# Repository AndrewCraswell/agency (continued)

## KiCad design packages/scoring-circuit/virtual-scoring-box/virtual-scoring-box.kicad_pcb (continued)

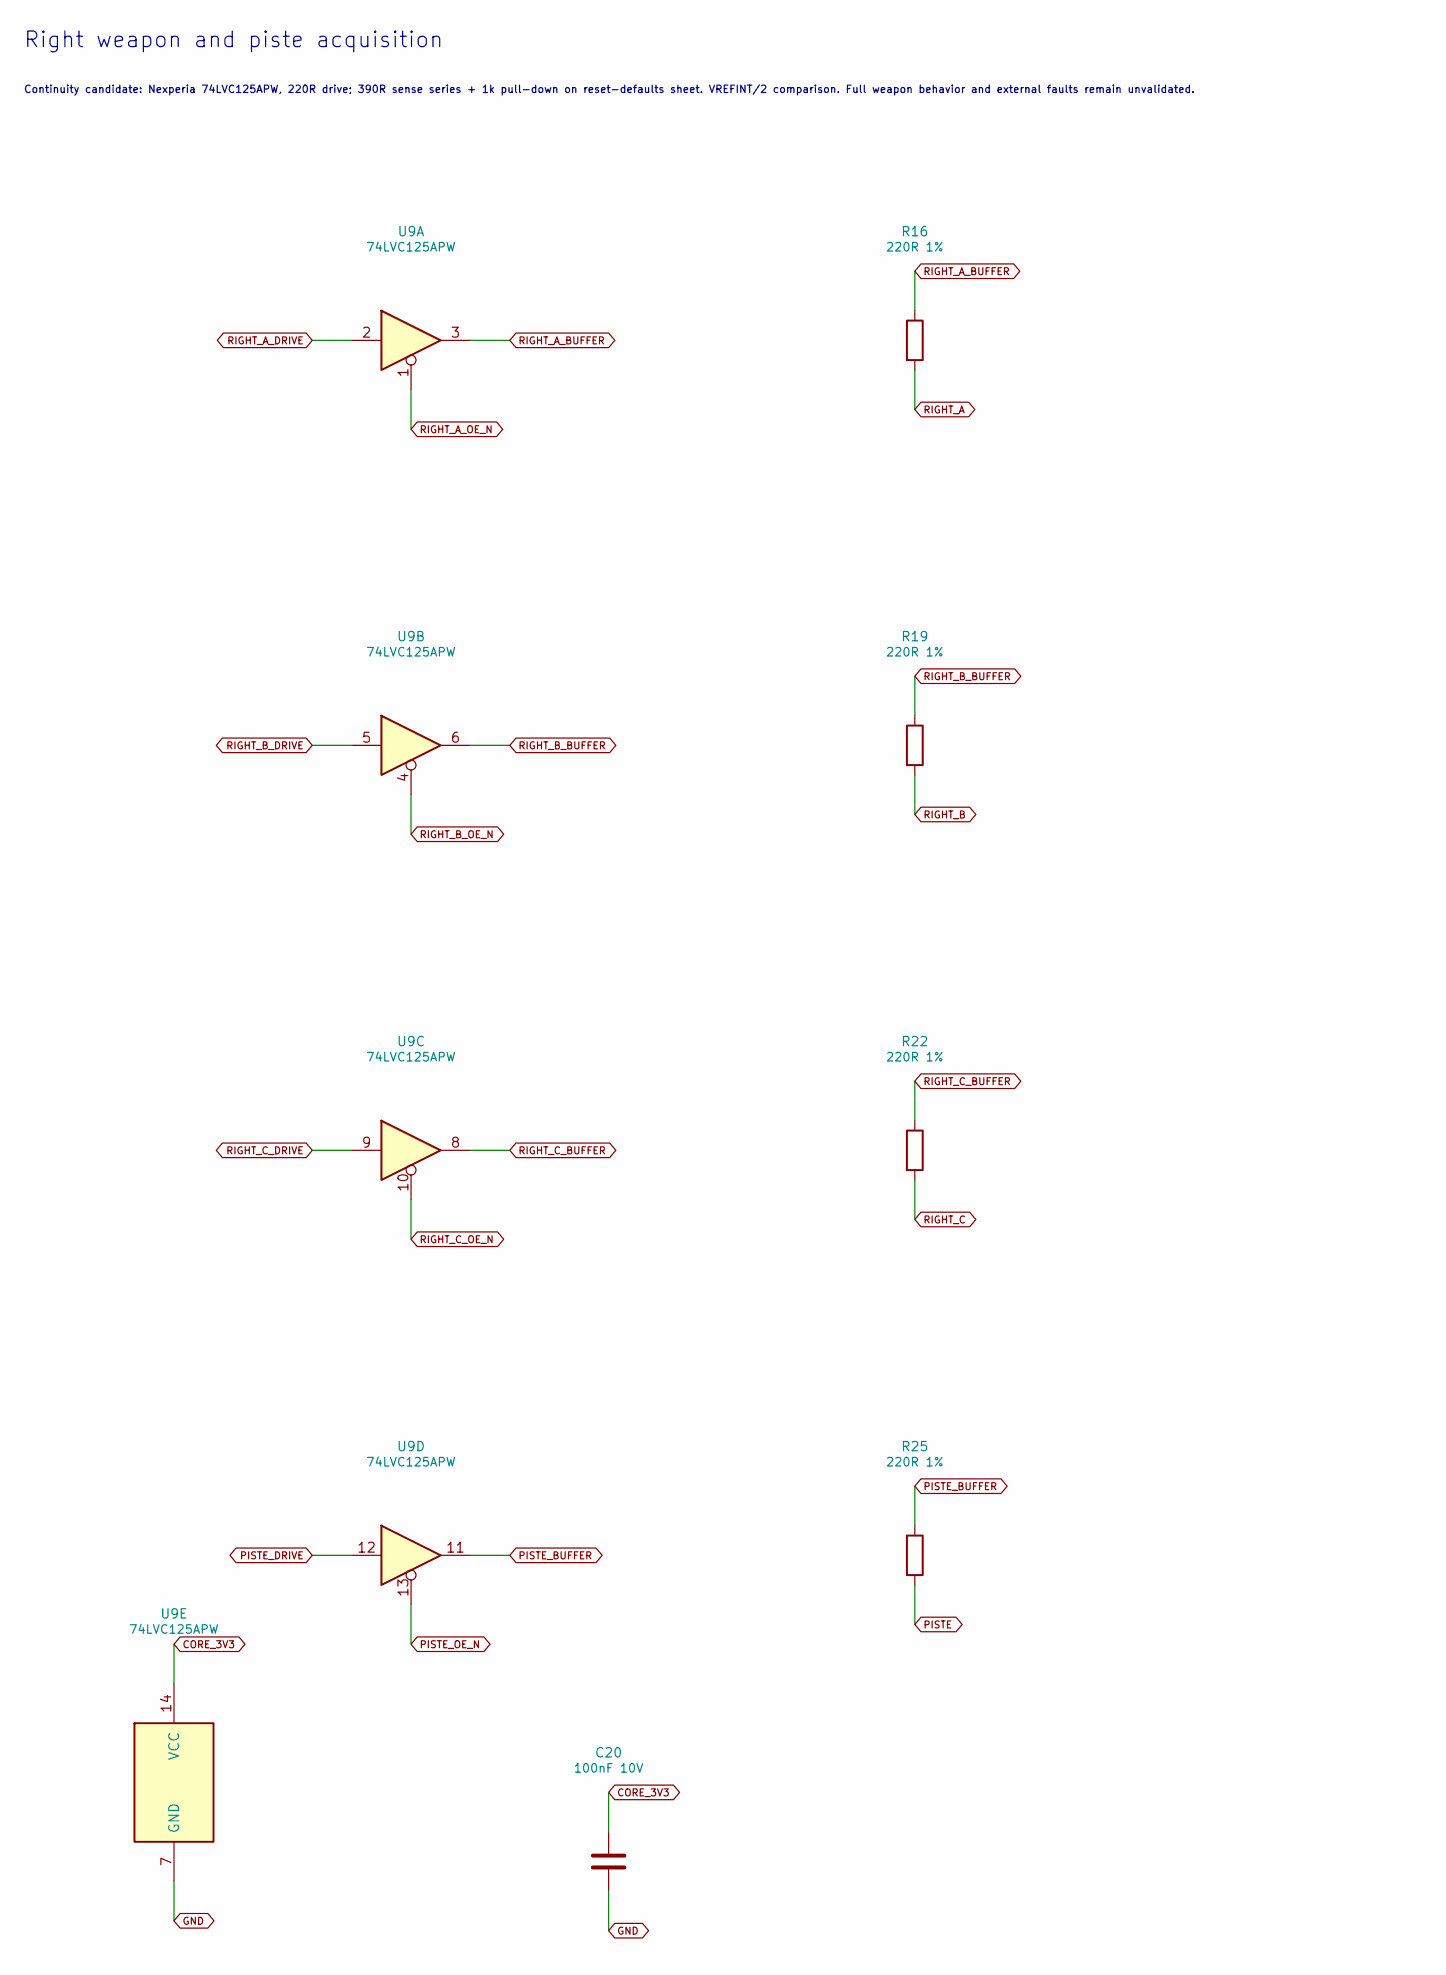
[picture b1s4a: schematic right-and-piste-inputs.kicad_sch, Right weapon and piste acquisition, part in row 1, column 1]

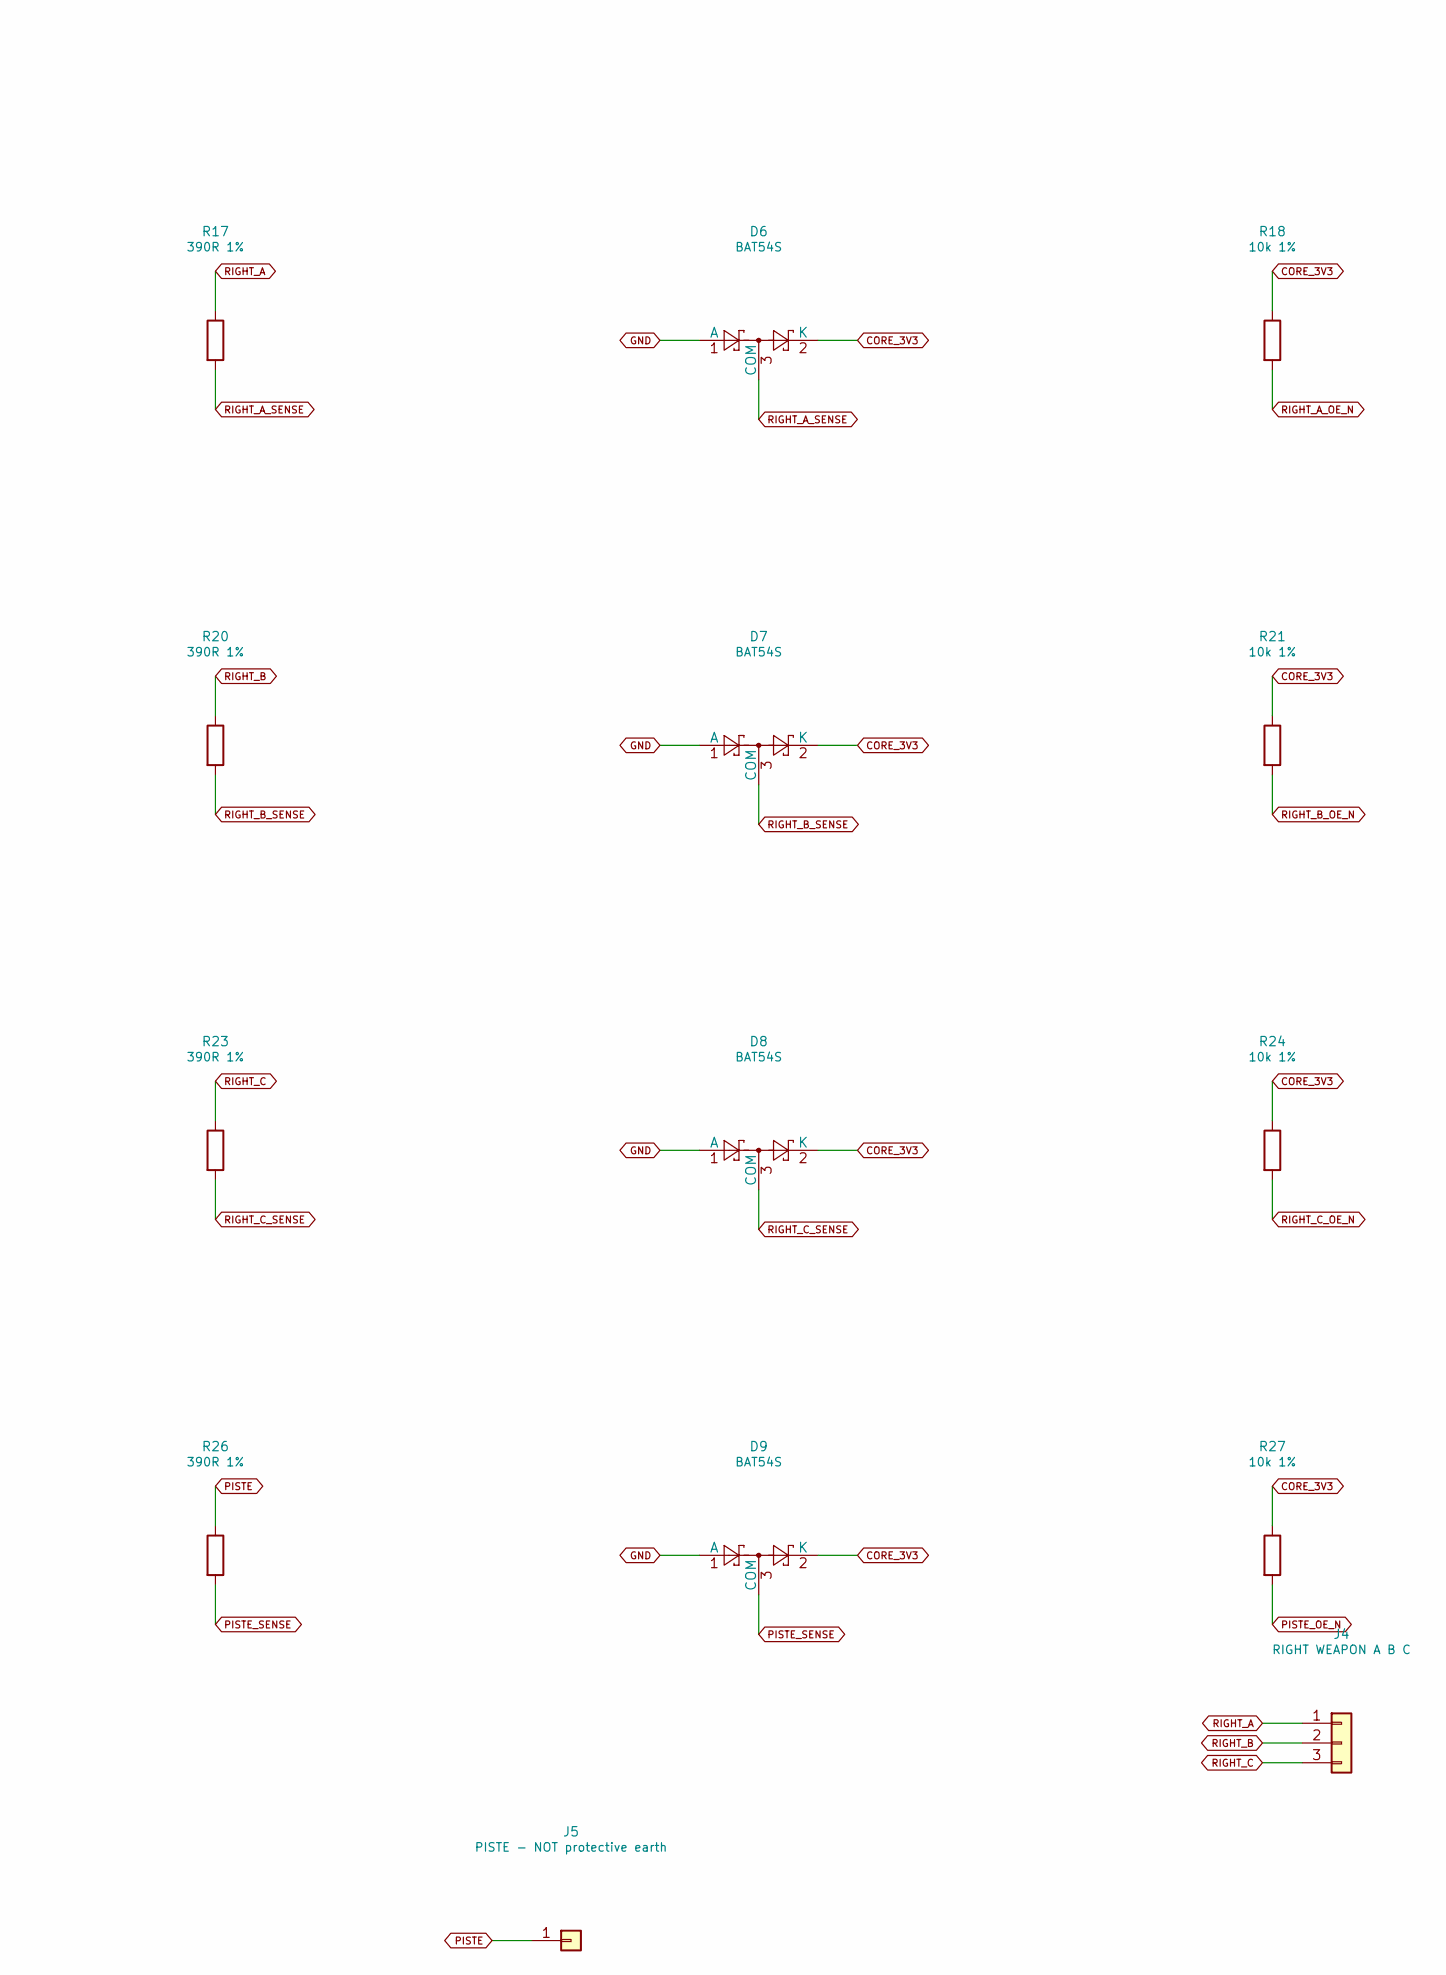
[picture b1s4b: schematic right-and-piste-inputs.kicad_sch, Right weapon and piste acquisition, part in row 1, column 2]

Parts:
C20: 100nF 10V; C_0603_1608Metric; MPN CC0603KRX7R9BB104
D6, D7, D8, D9: BAT54S; SOT-23; MPN BAT54S,215
J4: RIGHT WEAPON A B C; Wire_Solder_3; MPN PCB solder termination
J5: PISTE - NOT protective earth; Wire_Solder_1; MPN PCB solder termination
R16, R19, R22, R25: 220R 1%; R_0603_1608Metric; MPN ERJPA3F2200V
R17, R20, R23, R26: 390R 1%; R_0603_1608Metric; MPN RC0603FR-07390RL
R18, R21, R24, R27: 10k 1%; R_0603_1608Metric; MPN RC0603FR-0710KL
U9: 74LVC125APW; TSSOP-14_4.4x5mm_P0.65mm; MPN 74LVC125APW,118

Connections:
CORE_3V3: C20.1, D6.2 (K), D7.2 (K), D8.2 (K), D9.2 (K), R18.1, R21.1, R24.1, R27.1, U9.14 (VCC); also elsewhere on the board
GND: C20.2, D6.1 (A), D7.1 (A), D8.1 (A), D9.1 (A), U9.7 (GND); also elsewhere on the board
PISTE: J5.1 (Pin_1_1), R25.2, R26.1
PISTE_BUFFER: R25.1, U9.11
PISTE_DRIVE: U9.12; also elsewhere on the board
PISTE_OE_N: R27.2, U9.13; also elsewhere on the board
PISTE_SENSE: D9.3 (COM), R26.2; also elsewhere on the board
RIGHT_A: J4.1, R16.2, R17.1
RIGHT_A_BUFFER: R16.1, U9.3
RIGHT_A_DRIVE: U9.2; also elsewhere on the board
RIGHT_A_OE_N: R18.2, U9.1; also elsewhere on the board
RIGHT_A_SENSE: D6.3 (COM), R17.2; also elsewhere on the board
RIGHT_B: J4.2, R19.2, R20.1
RIGHT_B_BUFFER: R19.1, U9.6
RIGHT_B_DRIVE: U9.5; also elsewhere on the board
RIGHT_B_OE_N: R21.2, U9.4; also elsewhere on the board
RIGHT_B_SENSE: D7.3 (COM), R20.2; also elsewhere on the board
RIGHT_C: J4.3, R22.2, R23.1
RIGHT_C_BUFFER: R22.1, U9.8
RIGHT_C_DRIVE: U9.9; also elsewhere on the board
RIGHT_C_OE_N: R24.2, U9.10; also elsewhere on the board
RIGHT_C_SENSE: D8.3 (COM), R23.2; also elsewhere on the board

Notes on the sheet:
Right weapon and piste acquisition
Continuity candidate: Nexperia 74LVC125APW, 220R drive; 390R sense series + 1k pull-down on reset-defaults sheet. VREFINT/2 comparison. Full weapon behavior and external faults remain unvalidated.

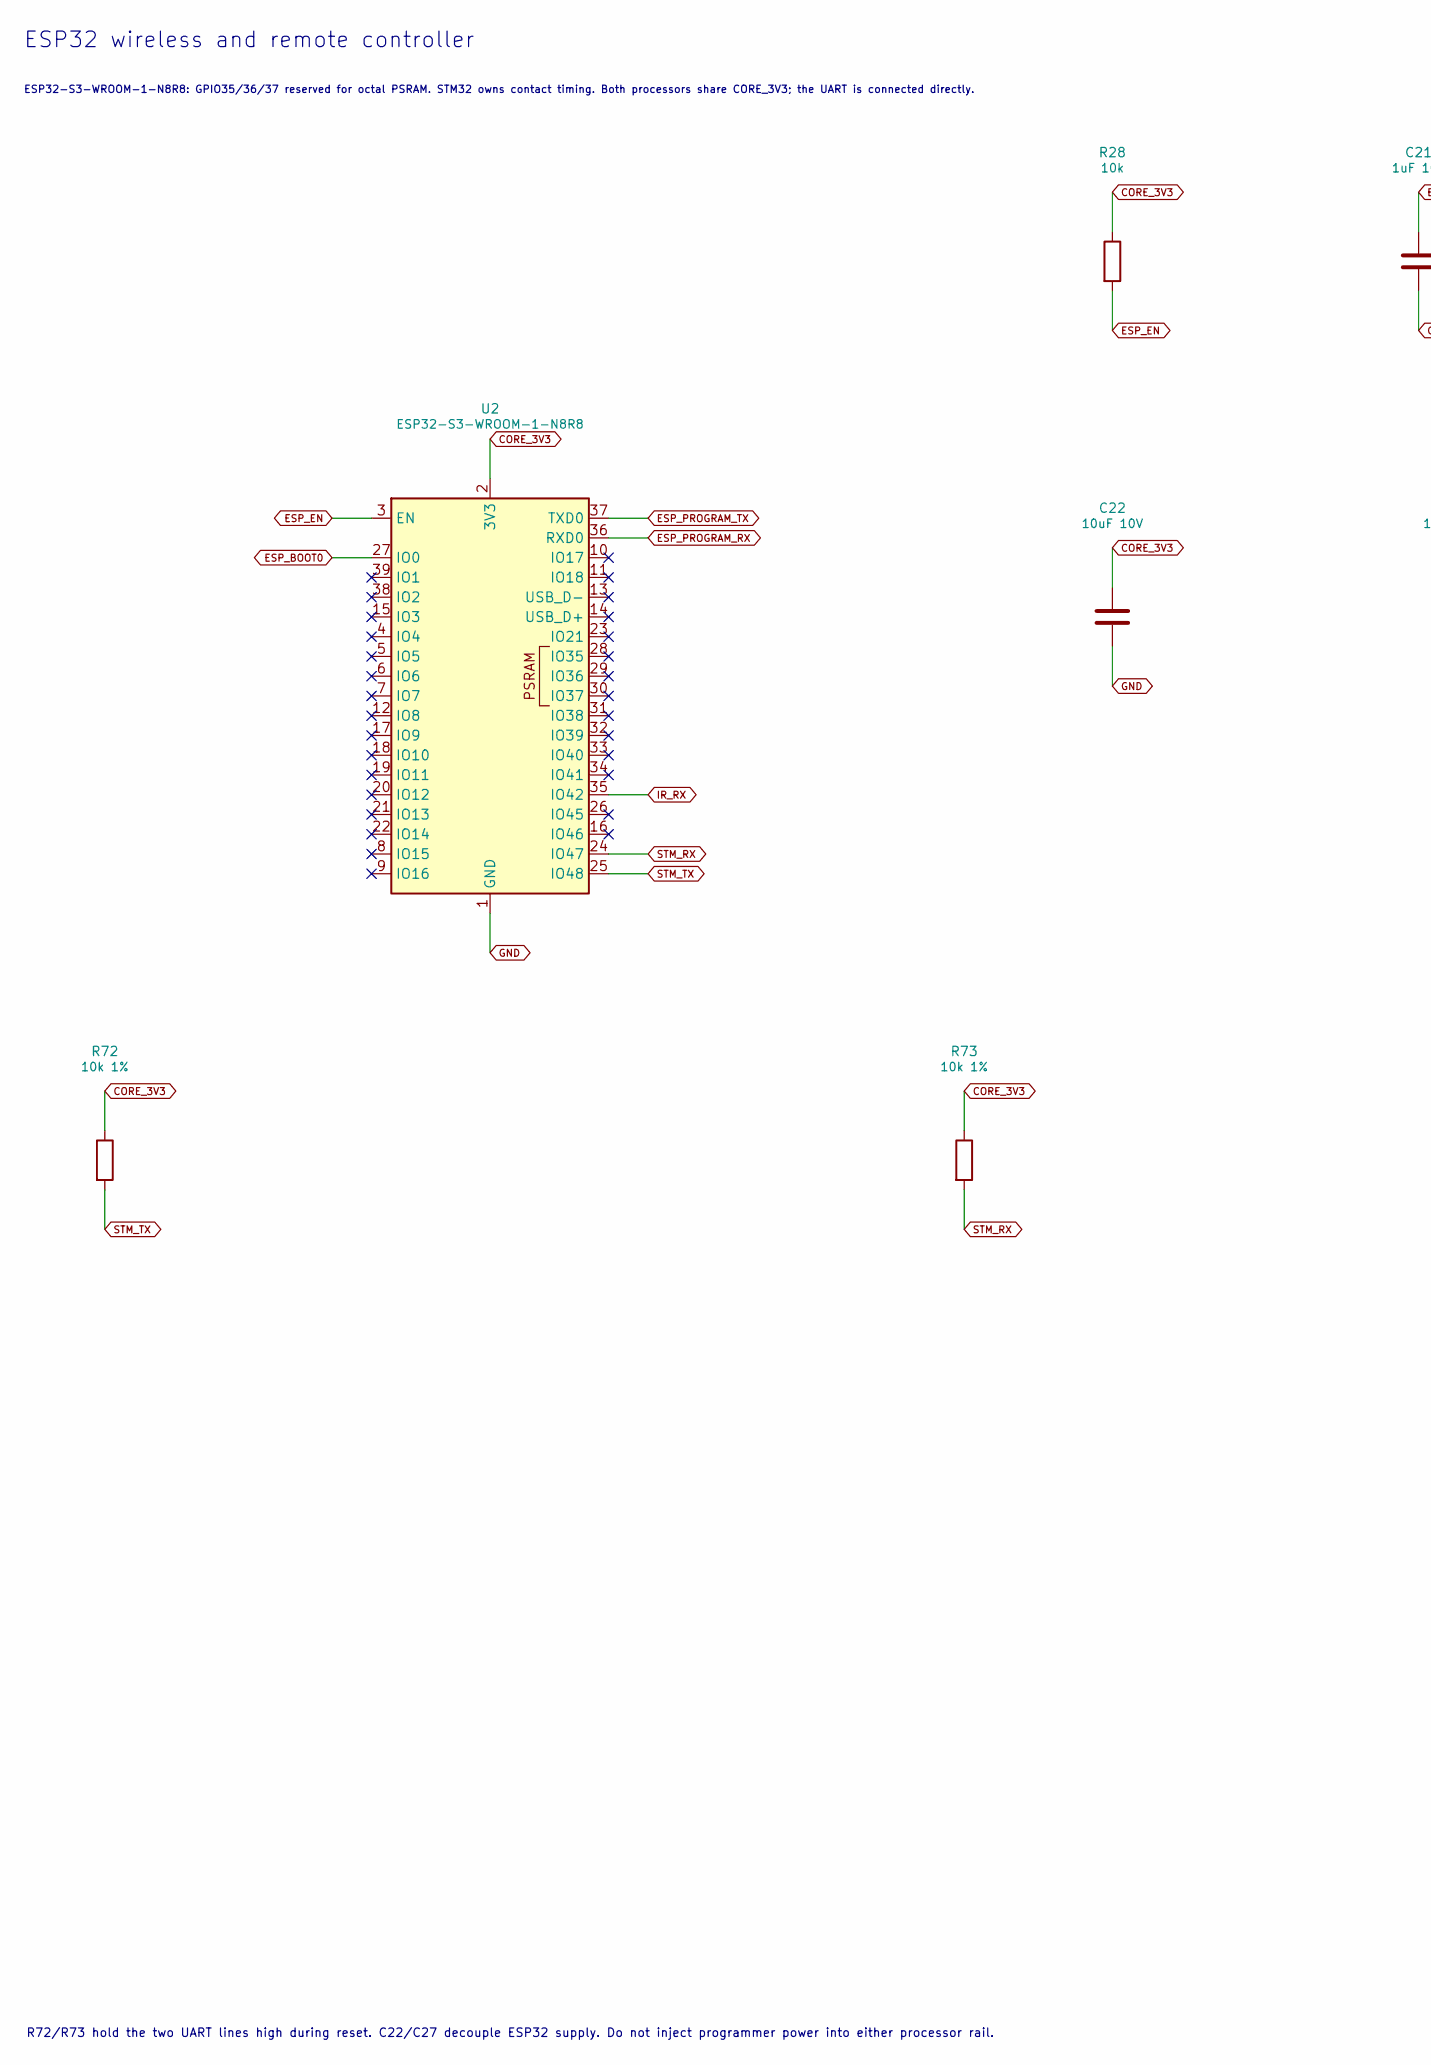
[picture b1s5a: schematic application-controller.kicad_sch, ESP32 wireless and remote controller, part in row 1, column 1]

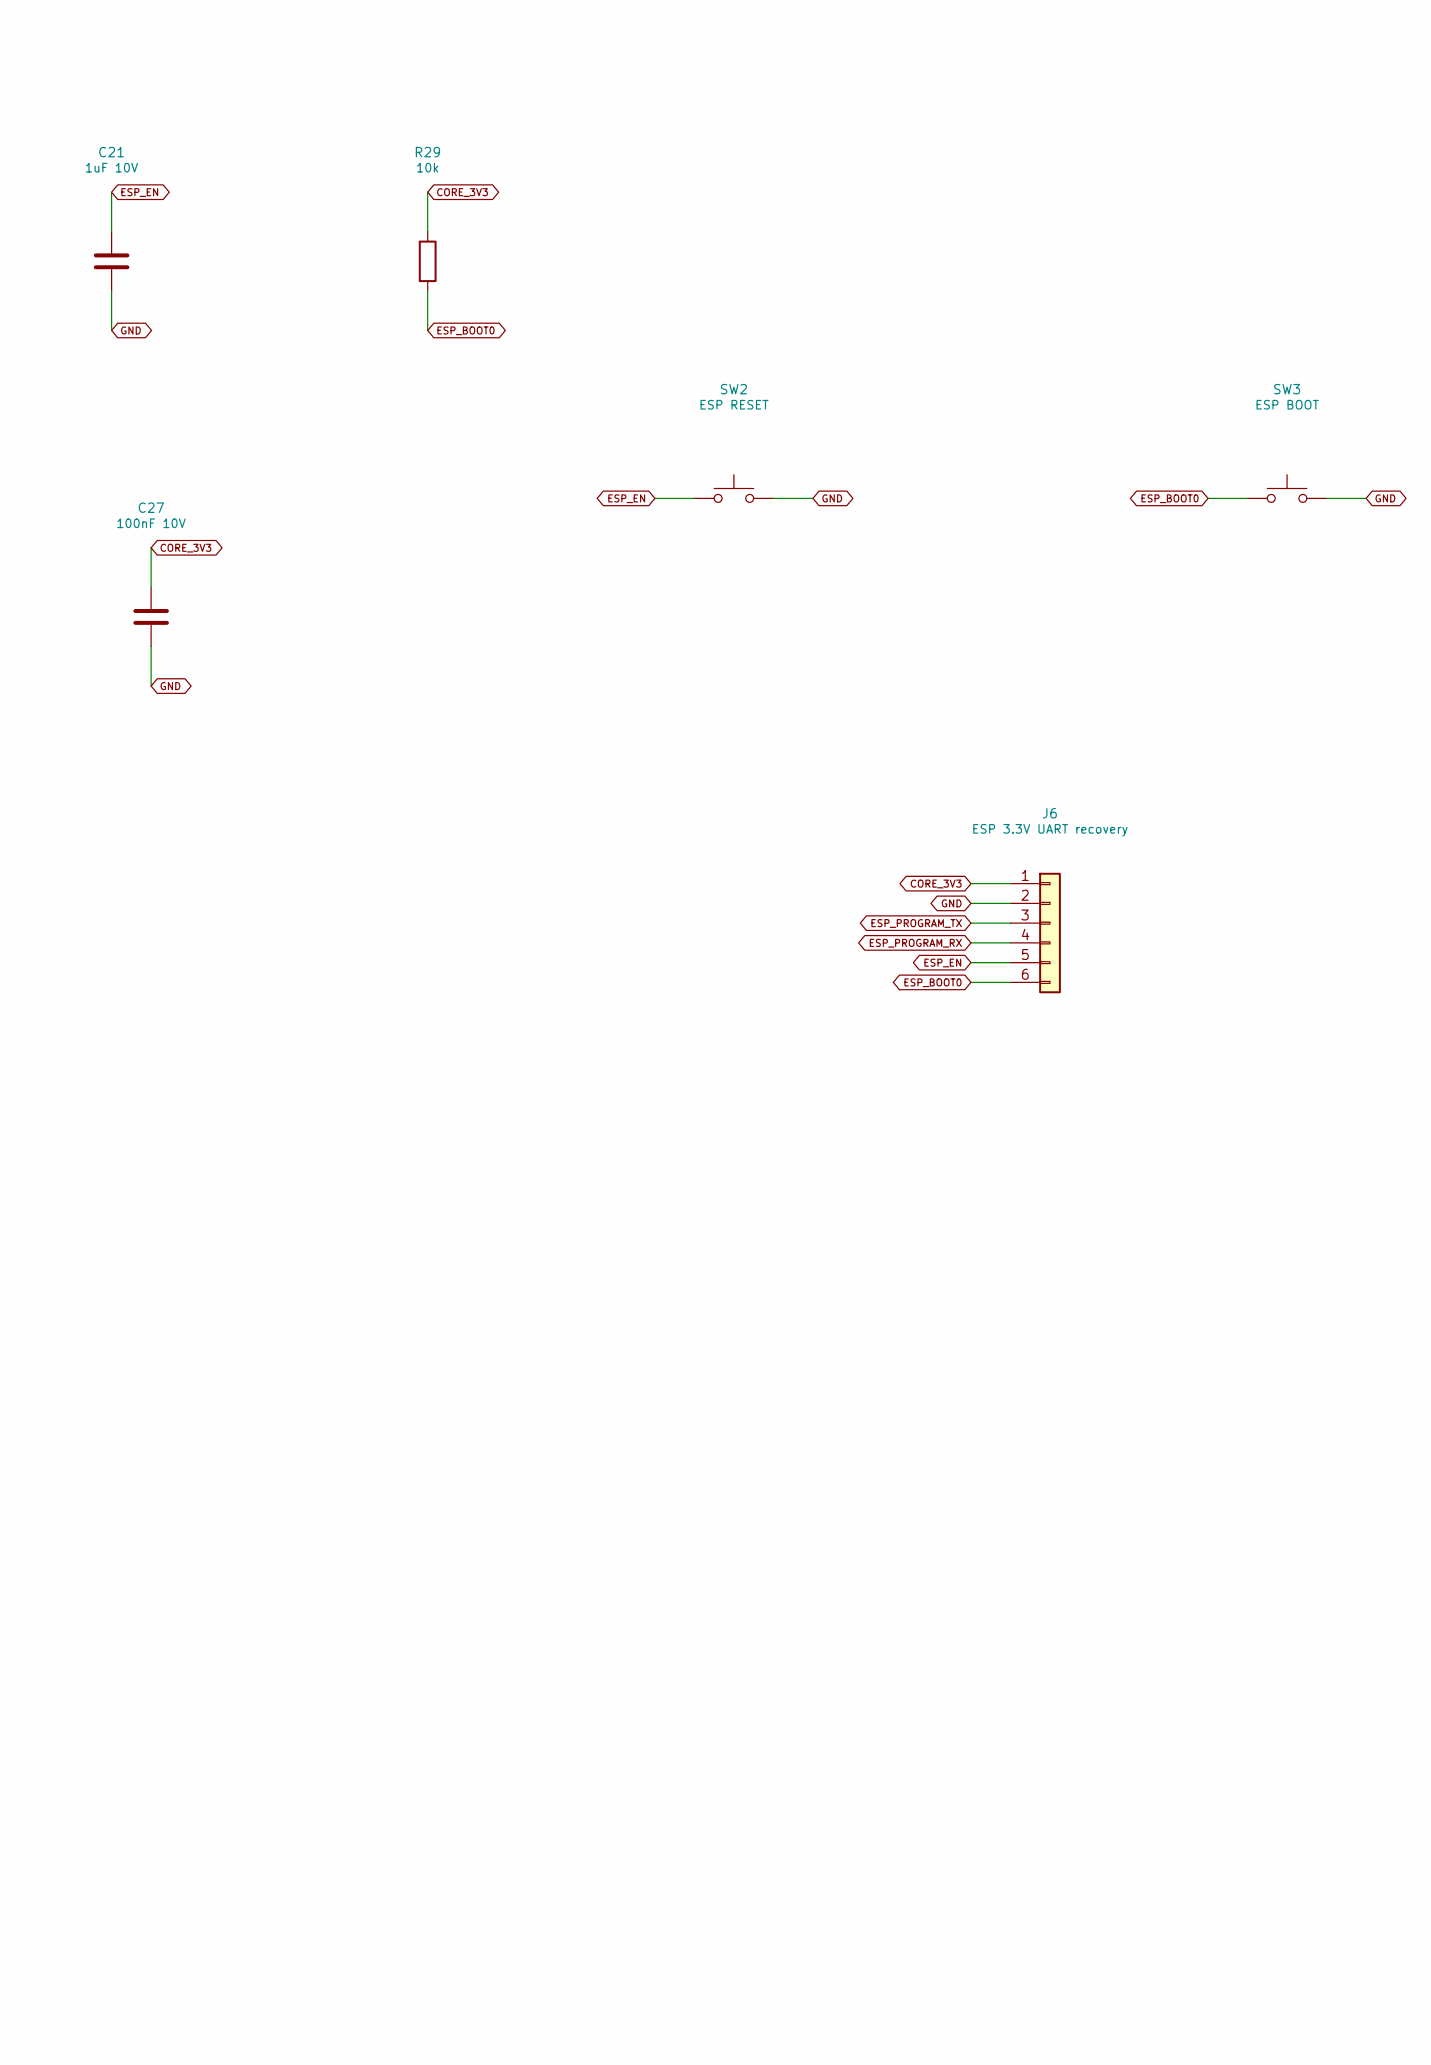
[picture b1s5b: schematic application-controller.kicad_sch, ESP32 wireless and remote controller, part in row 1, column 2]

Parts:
C21: 1uF 10V; C_0603_1608Metric; MPN CC0603KRX7R9BB105; JLCPCB C559769
C22: 10uF 10V; C_0603_1608Metric; MPN C1608X5R1C106MT000N; JLCPCB C342854
C27: 100nF 10V; C_0603_1608Metric; MPN CC0603KRX7R9BB104
J6: ESP 3.3V UART recovery; Samtec_HTSW-106-07-L-S; MPN HTSW-106-07-G-S; JLCPCB C3334125
R28, R29: 10k; R_0603_1608Metric; MPN RC0603FR-0710KL
R72, R73: 10k 1%; R_0603_1608Metric; MPN RC0603FR-0710KL
SW2: ESP RESET; SW_SPST_TL3342; MPN TL3342F160QG
SW3: ESP BOOT; SW_SPST_TL3342; MPN TL3342F160QG
U2: ESP32-S3-WROOM-1-N8R8; ESP32-S3-WROOM-1_Edge; MPN ESP32-S3-WROOM-1-N8R8

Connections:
CORE_3V3: C22.1, C27.1, J6.1, R28.1, R29.1, R72.1, R73.1, U2.2 (3V3); also elsewhere on the board
ESP_BOOT0: J6.6, R29.2, SW3.1, U2.27 (IO0)
ESP_EN: C21.1, J6.5, R28.2, SW2.1, U2.3 (EN)
ESP_PROGRAM_RX: J6.4, U2.36 (RXD0)
ESP_PROGRAM_TX: J6.3, U2.37 (TXD0)
GND: C21.2, C22.2, C27.2, J6.2, SW2.2, SW3.2, U2.1 (GND), U2.40 (GND), U2.41 (GND); also elsewhere on the board
IR_RX: U2.35 (IO42); also elsewhere on the board
STM_RX: R73.2, U2.24 (IO47); also elsewhere on the board
STM_TX: R72.2, U2.25 (IO48); also elsewhere on the board

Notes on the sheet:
ESP32 wireless and remote controller
ESP32-S3-WROOM-1-N8R8: GPIO35/36/37 reserved for octal PSRAM. STM32 owns contact timing. Both processors share CORE_3V3; the UART is connected directly.
R72/R73 hold the two UART lines high during reset. C22/C27 decouple ESP32 supply. Do not inject programmer power into either processor rail.

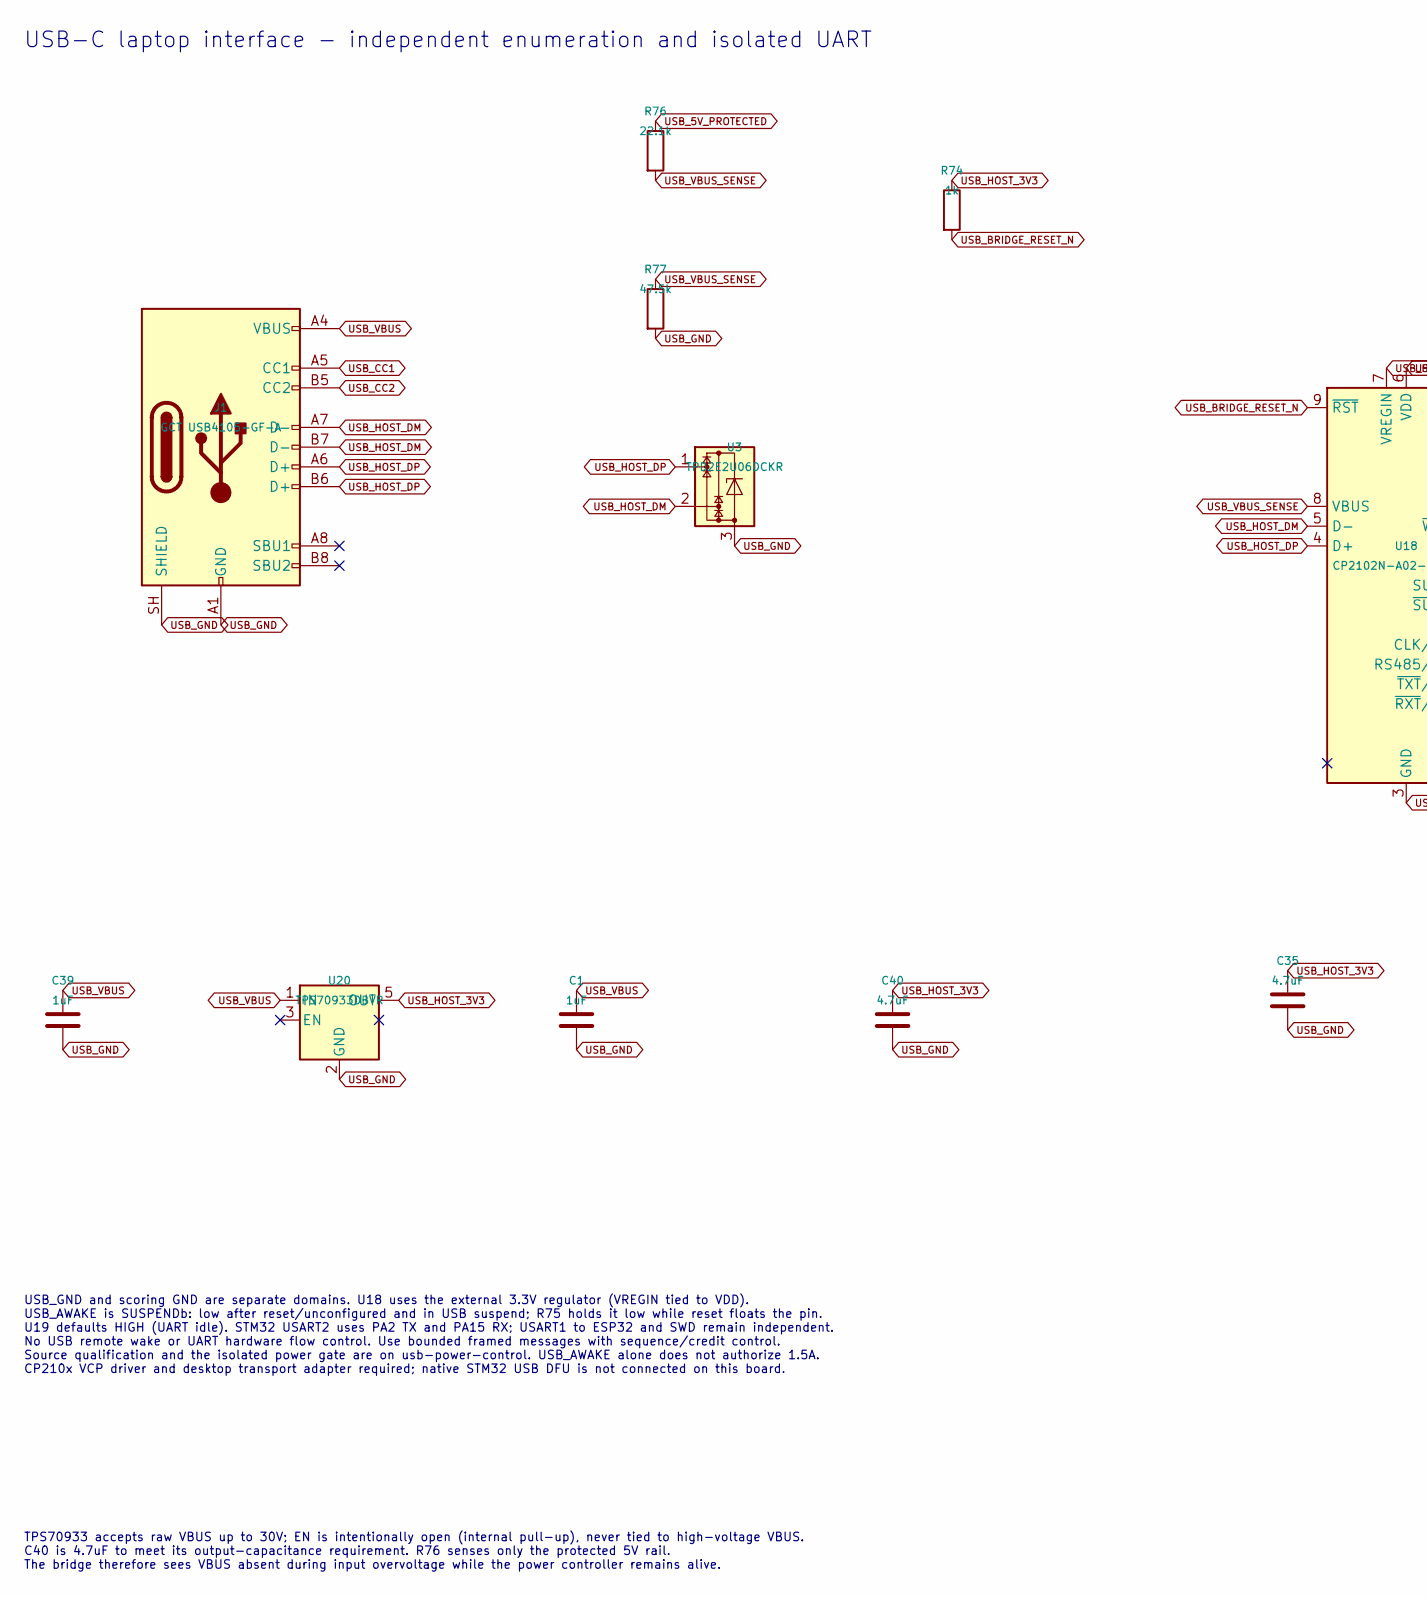
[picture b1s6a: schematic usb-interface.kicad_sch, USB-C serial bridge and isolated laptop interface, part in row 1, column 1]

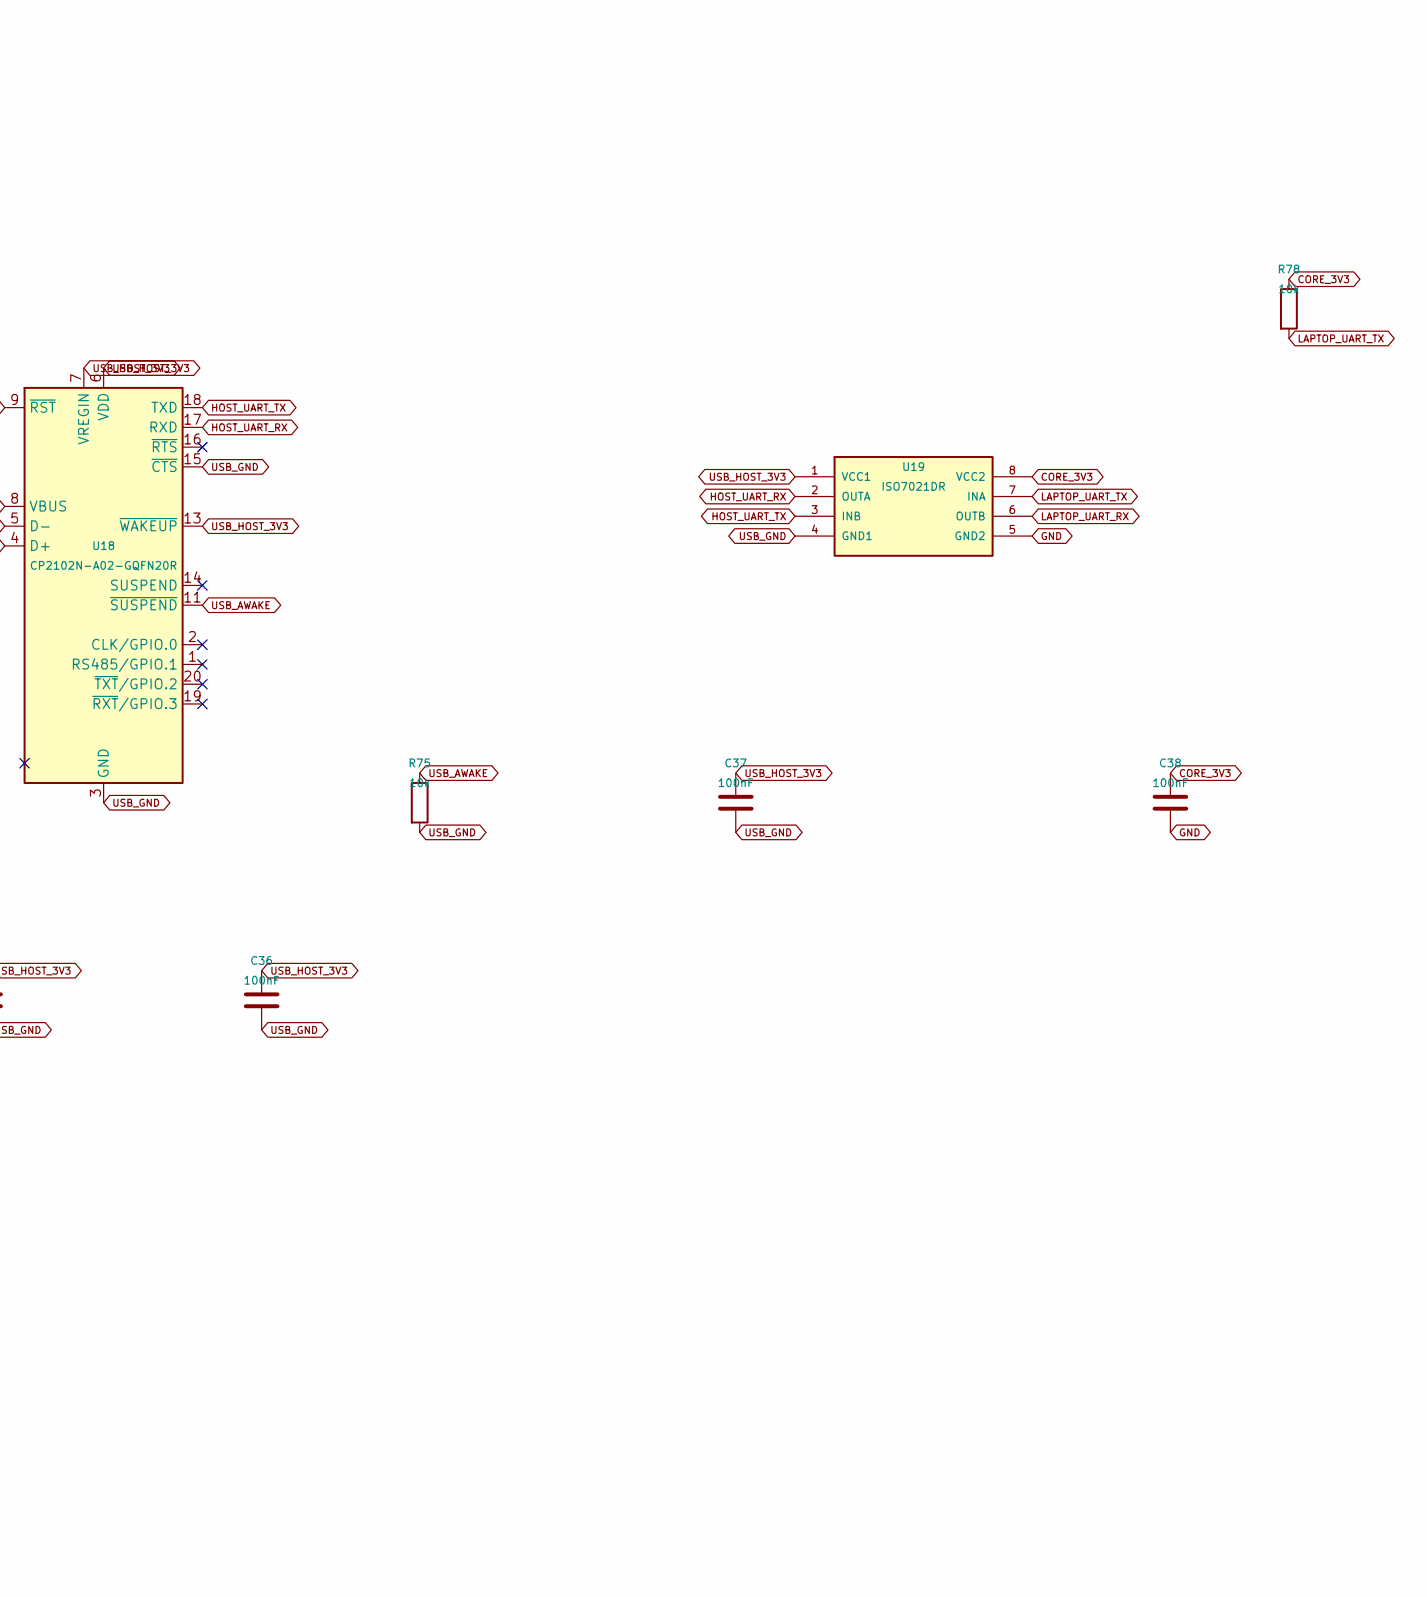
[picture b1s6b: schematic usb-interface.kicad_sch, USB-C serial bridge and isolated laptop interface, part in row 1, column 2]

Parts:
C1, C39: 1uF; C_0603_1608Metric; MPN CC0603KRX7R9BB105; JLCPCB C559769
C35, C40: 4.7uF; C_0603_1608Metric; MPN GRM188R61A475KE15D
C36, C37, C38: 100nF; C_0603_1608Metric; MPN CC0603KRX7R9BB104
J1: GCT USB4105-GF-A; USB4105_GF_A; MPN USB4105-GF-A
R74: 1k; R_0603_1608Metric; MPN RC0603FR-071KL
R75, R78: 10k; R_0603_1608Metric; MPN RC0603FR-0710KL
R76: 22.1k; R_0603_1608Metric; MPN RC0603FR-0722K1L
R77: 47.5k; R_0603_1608Metric; MPN RC0603FR-0747K5L
U3: TPD2E2U06DCKR; MPN TPD2E2U06DCKR
U18: CP2102N-A02-GQFN20R; CP2102N_QFN20; MPN CP2102N-A02-GQFN20R
U19: ISO7021DR; SOIC-8_3.9x4.9mm_P1.27mm; MPN ISO7021DR
U20: TPS70933DBVR; SOT-23-5; MPN TPS70933DBVR

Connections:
CORE_3V3: C38.1, R78.1, U19.8 (VCC2); also elsewhere on the board
GND: C38.2, U19.5 (GND2); also elsewhere on the board
HOST_UART_RX: U18.17 (RXD), U19.2 (OUTA)
HOST_UART_TX: U18.18 (TXD), U19.3 (INB)
LAPTOP_UART_RX: U19.6 (OUTB); also elsewhere on the board
LAPTOP_UART_TX: R78.2, U19.7 (INA); also elsewhere on the board
USB_5V_PROTECTED: R76.1; also elsewhere on the board
USB_AWAKE: R75.1, U18.11 (~SUSPEND); also elsewhere on the board
USB_BRIDGE_RESET_N: R74.2, U18.9 (~RST)
USB_CC1: J1.A5 (CC1); also elsewhere on the board
USB_CC2: J1.B5 (CC2); also elsewhere on the board
USB_GND: C1.2, C35.2, C36.2, C37.2, C39.2, C40.2, J1.A1 (GND), J1.A12 (GND), J1.B1 (GND), J1.B12 (GND), J1.SH (SHIELD), R75.2, R77.2, U3.3, U18.3 (GND), U18.12 (GND), U18.15 (~CTS), U18.21 (GND), U19.4 (GND1), U20.2 (GND); also elsewhere on the board
USB_HOST_3V3: C35.1, C36.1, C37.1, C40.1, R74.1, U18.6 (VDD), U18.7 (VREGIN), U18.13 (~WAKEUP), U19.1 (VCC1), U20.5 (OUT); also elsewhere on the board
USB_HOST_DM: J1.A7 (D-), J1.B7 (D-), U3.2, U18.5 (D-)
USB_HOST_DP: J1.A6 (D+), J1.B6 (D+), U3.1, U18.4 (D+)
USB_VBUS: C1.1, C39.1, J1.A4 (VBUS), J1.A9 (VBUS), J1.B4 (VBUS), J1.B9 (VBUS), U20.1 (IN); also elsewhere on the board
USB_VBUS_SENSE: R76.2, R77.1, U18.8 (VBUS)

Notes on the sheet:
USB-C laptop interface - independent enumeration and isolated UART
USB_GND and scoring GND are separate domains. U18 uses the external 3.3V regulator (VREGIN tied to VDD). USB_AWAKE is SUSPENDb: low after reset/unconfigured and in USB suspend; R75 holds it low while reset floats the pin. U19 defaults HIGH (UART idle). STM32 USART2 uses PA2 TX and PA15 RX; USART1 t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
TPS70933 accepts raw VBUS up to 30V; EN is intentionally open (internal pull-up), never tied to high-voltage VBUS. C40 is 4.7uF to meet its output-capacitance requirement. R76 senses only the protected 5V rail. The bridge therefore sees VBUS absent during input overvoltage while the power controlle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
